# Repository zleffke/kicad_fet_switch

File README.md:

# kicad_fet_switch
High Current, DC, High Side, P-Channel MOSFET Switch.  Based on W6PQL design.

### Credit where its due:
[High Current DC Switch](https://www.w6pql.com/high_current_solid-state_dc_switch.htm) from W6PQL.

This design is the identical circuit, just a kicad implementation and variations on the layout for my own projects.

#### Versions:

high_current_v1 - initial prototype design, fixed resistors, no mounting screw, all SMT.
 - Rev- sent to Osh Park, 20200601

high_current_v2 - Same base design, variable resistors for R1, R5, R6 to set for any range up to ~50V.

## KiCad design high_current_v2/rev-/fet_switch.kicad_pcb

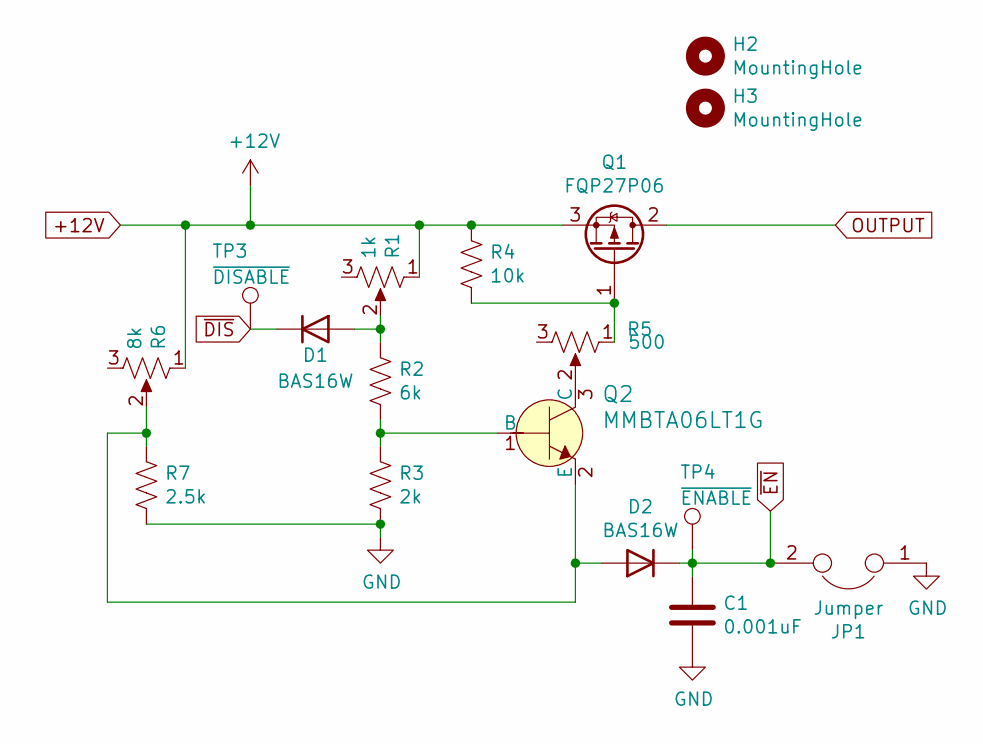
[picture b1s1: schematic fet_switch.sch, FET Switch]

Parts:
C1: 0.001uF; 0805
D1, D2: BAS16W; SOT-323_SC-70
H2, H3: MountingHole; MountingHole_3.2mm_M3
JP1: Jumper; SolderJumper-2_P1.3mm_Open_TrianglePad1.0x1.5mm
Q1: FQP27P06; TO-263-2
Q2: MMBTA06LT1G; SOT-23-3; MPN MMBTA06LT1G; Digi-Key_PN MMBTA06LT1GOSCT-ND
R1: 1k; Potentiometer_Bourns_3314G_Vertical
R2: 6k; 0805
R3: 2k; 0805
R4: 10k; 0805
R5: 500; Potentiometer_Bourns_3314G_Vertical
R6: 8k; Potentiometer_Bourns_3314G_Vertical
R7: 2.5k; 0805
TP3: ~DISABLE; TestPoint_Pad_2.0x2.0mm
TP4: ~ENABLE; TestPoint_Pad_2.0x2.0mm

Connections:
+12V: Q1.3 (S), R1.1, R4.1, R6.1
GND: C1.2, JP1.1, R3.2, R7.2
unnamed: D1.1 (A), R1.2, R2.1
unnamed: D2.1 (A), Q2.2 (E), R6.2, R7.1
unnamed: Q1.1 (G), R4.2, R5.1
unnamed: Q2.1 (B), R2.2, R3.1
unnamed: Q2.3 (C), R5.2
OUTPUT: Q1.2 (D)
~DIS: D1.3 (K), TP3.1
~EN: C1.1, D2.3 (K), JP1.2, TP4.1

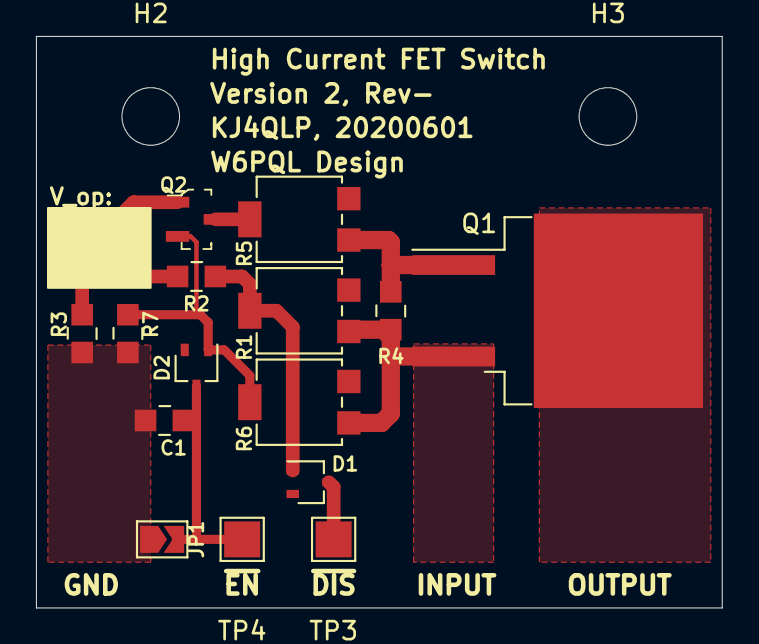
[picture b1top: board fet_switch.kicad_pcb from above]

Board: 2 copper layers, 38.1 x 31.8 mm, 17 parts (0 on the bottom side), 9 nets.

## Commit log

2020-06-01 completed design, this commit sent to osh park.
2020-06-01 fixed silkscreen...resistor identifiers changed to match W6PQL schematic and table.
2020-06-01 updated figures...this commit submitted to osh park, previous commit note was cancelled.
2020-06-01 version 2, rev-, complete design with trimpots. this commit submitted to osh park.
2020-06-01 updated v2 figures
2020-06-09 adding schematic PDFs
2021-02-22 adding purchase list

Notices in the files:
high_current_v1/rev-/fet_switch.sch:
creativecommons.org/licenses/by/4.0
License: CC BY 4.0
